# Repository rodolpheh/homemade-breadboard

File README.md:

This is a quick design of an homemade breadboard. This design has not been tested yet. It features 20 rows and 2 power lines on each side.

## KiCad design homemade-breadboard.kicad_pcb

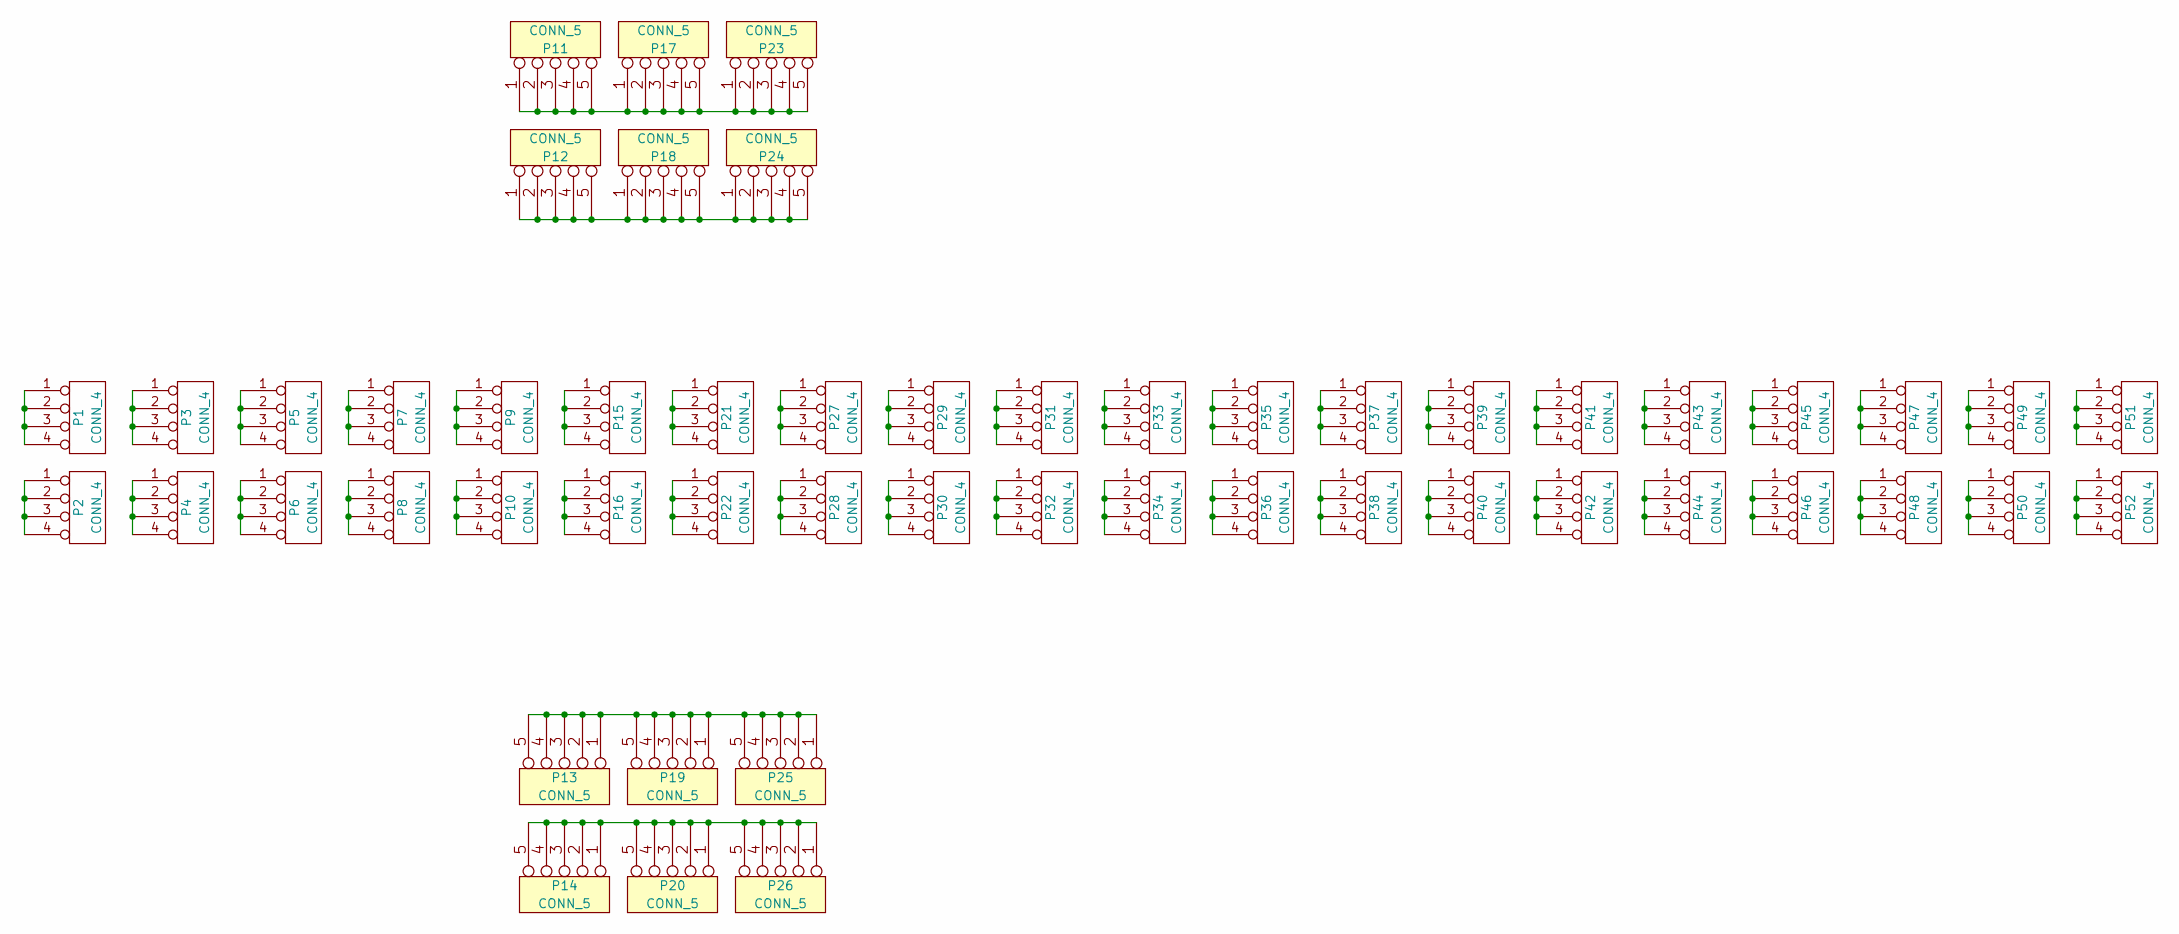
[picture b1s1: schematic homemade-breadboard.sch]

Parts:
P1, P2, P3, P4, P5, P6, P7, P8, P9, P10, P15, P16, P21, P22, P27, P28, P29, P30, P31, P32, P33, P34, P35, P36, P37, P38, P39, P40, P41, P42, P43, P44, P45, P46, P47, P48, P49, P50, P51, P52: CONN_4
P11, P12, P13, P14, P17, P18, P19, P20, P23, P24, P25, P26: CONN_5

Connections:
unnamed: P11.1, P11.2, P11.3, P11.4, P11.5, P17.1, P17.2, P17.3, P17.4, P17.5, P23.1, P23.2, P23.3, P23.4, P23.5
unnamed: P27.1, P27.2, P27.3, P27.4
unnamed: P21.1, P21.2, P21.3, P21.4
unnamed: P15.1, P15.2, P15.3, P15.4
unnamed: P29.1, P29.2, P29.3, P29.4
unnamed: P9.1, P9.2, P9.3, P9.4
unnamed: P7.1, P7.2, P7.3, P7.4
unnamed: P42.1, P42.2, P42.3, P42.4
unnamed: P40.1, P40.2, P40.3, P40.4
unnamed: P38.1, P38.2, P38.3, P38.4
unnamed: P5.1, P5.2, P5.3, P5.4
unnamed: P36.1, P36.2, P36.3, P36.4
unnamed: P34.1, P34.2, P34.3, P34.4
unnamed: P31.1, P31.2, P31.3, P31.4
unnamed: P16.1, P16.2, P16.3, P16.4
unnamed: P10.1, P10.2, P10.3, P10.4
unnamed: P8.1, P8.2, P8.3, P8.4
unnamed: P6.1, P6.2, P6.3, P6.4
unnamed: P4.1, P4.2, P4.3, P4.4
unnamed: P2.1, P2.2, P2.3, P2.4
unnamed: P3.1, P3.2, P3.3, P3.4
unnamed: P1.1, P1.2, P1.3, P1.4
unnamed: P32.1, P32.2, P32.3, P32.4
unnamed: P30.1, P30.2, P30.3, P30.4
unnamed: P28.1, P28.2, P28.3, P28.4
unnamed: P22.1, P22.2, P22.3, P22.4
unnamed: P51.1, P51.2, P51.3, P51.4
unnamed: P49.1, P49.2, P49.3, P49.4
unnamed: P47.1, P47.2, P47.3, P47.4
unnamed: P12.1, P12.2, P12.3, P12.4, P12.5, P18.1, P18.2, P18.3, P18.4, P18.5, P24.1, P24.2, P24.3, P24.4, P24.5
unnamed: P14.1, P14.2, P14.3, P14.4, P14.5, P20.1, P20.2, P20.3, P20.4, P20.5, P26.1, P26.2, P26.3, P26.4, P26.5
unnamed: P13.1, P13.2, P13.3, P13.4, P13.5, P19.1, P19.2, P19.3, P19.4, P19.5, P25.1, P25.2, P25.3, P25.4, P25.5
unnamed: P33.1, P33.2, P33.3, P33.4
unnamed: P52.1, P52.2, P52.3, P52.4
unnamed: P50.1, P50.2, P50.3, P50.4
unnamed: P48.1, P48.2, P48.3, P48.4
unnamed: P46.1, P46.2, P46.3, P46.4
unnamed: P44.1, P44.2, P44.3, P44.4
unnamed: P45.1, P45.2, P45.3, P45.4
unnamed: P43.1, P43.2, P43.3, P43.4
unnamed: P41.1, P41.2, P41.3, P41.4
unnamed: P39.1, P39.2, P39.3, P39.4
unnamed: P37.1, P37.2, P37.3, P37.4
unnamed: P35.1, P35.2, P35.3, P35.4

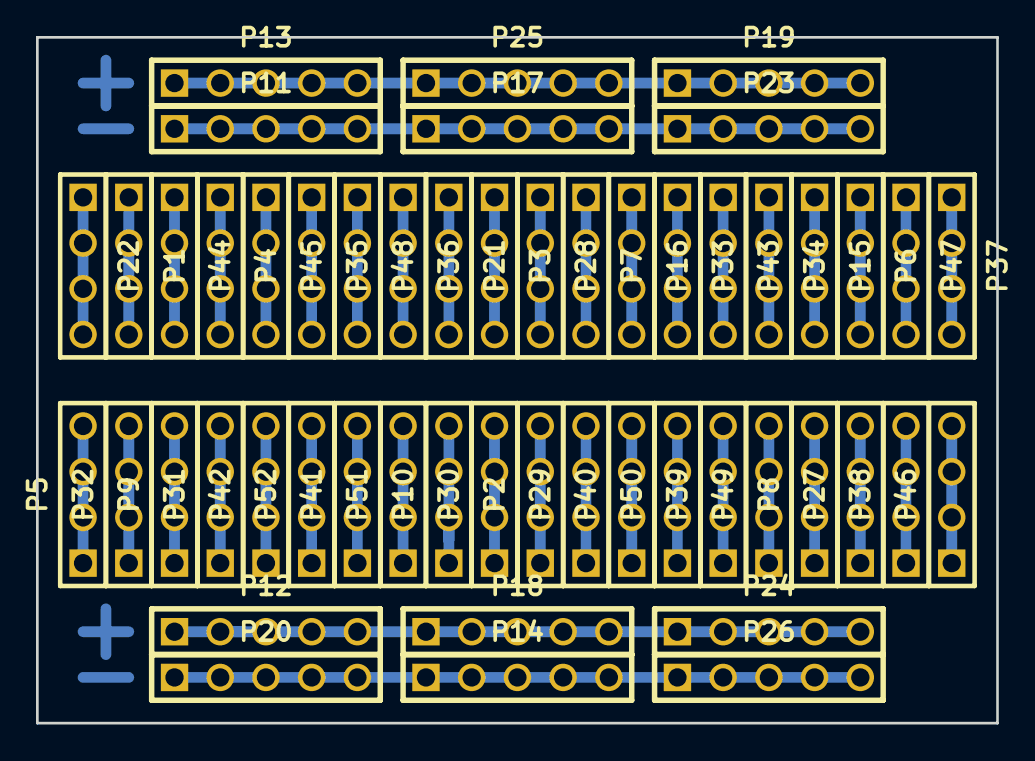
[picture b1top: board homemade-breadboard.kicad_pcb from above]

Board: 2 copper layers, 53.3 x 38.1 mm, 52 parts (0 on the bottom side), 44 nets.

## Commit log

2014-05-15 Adding picture
